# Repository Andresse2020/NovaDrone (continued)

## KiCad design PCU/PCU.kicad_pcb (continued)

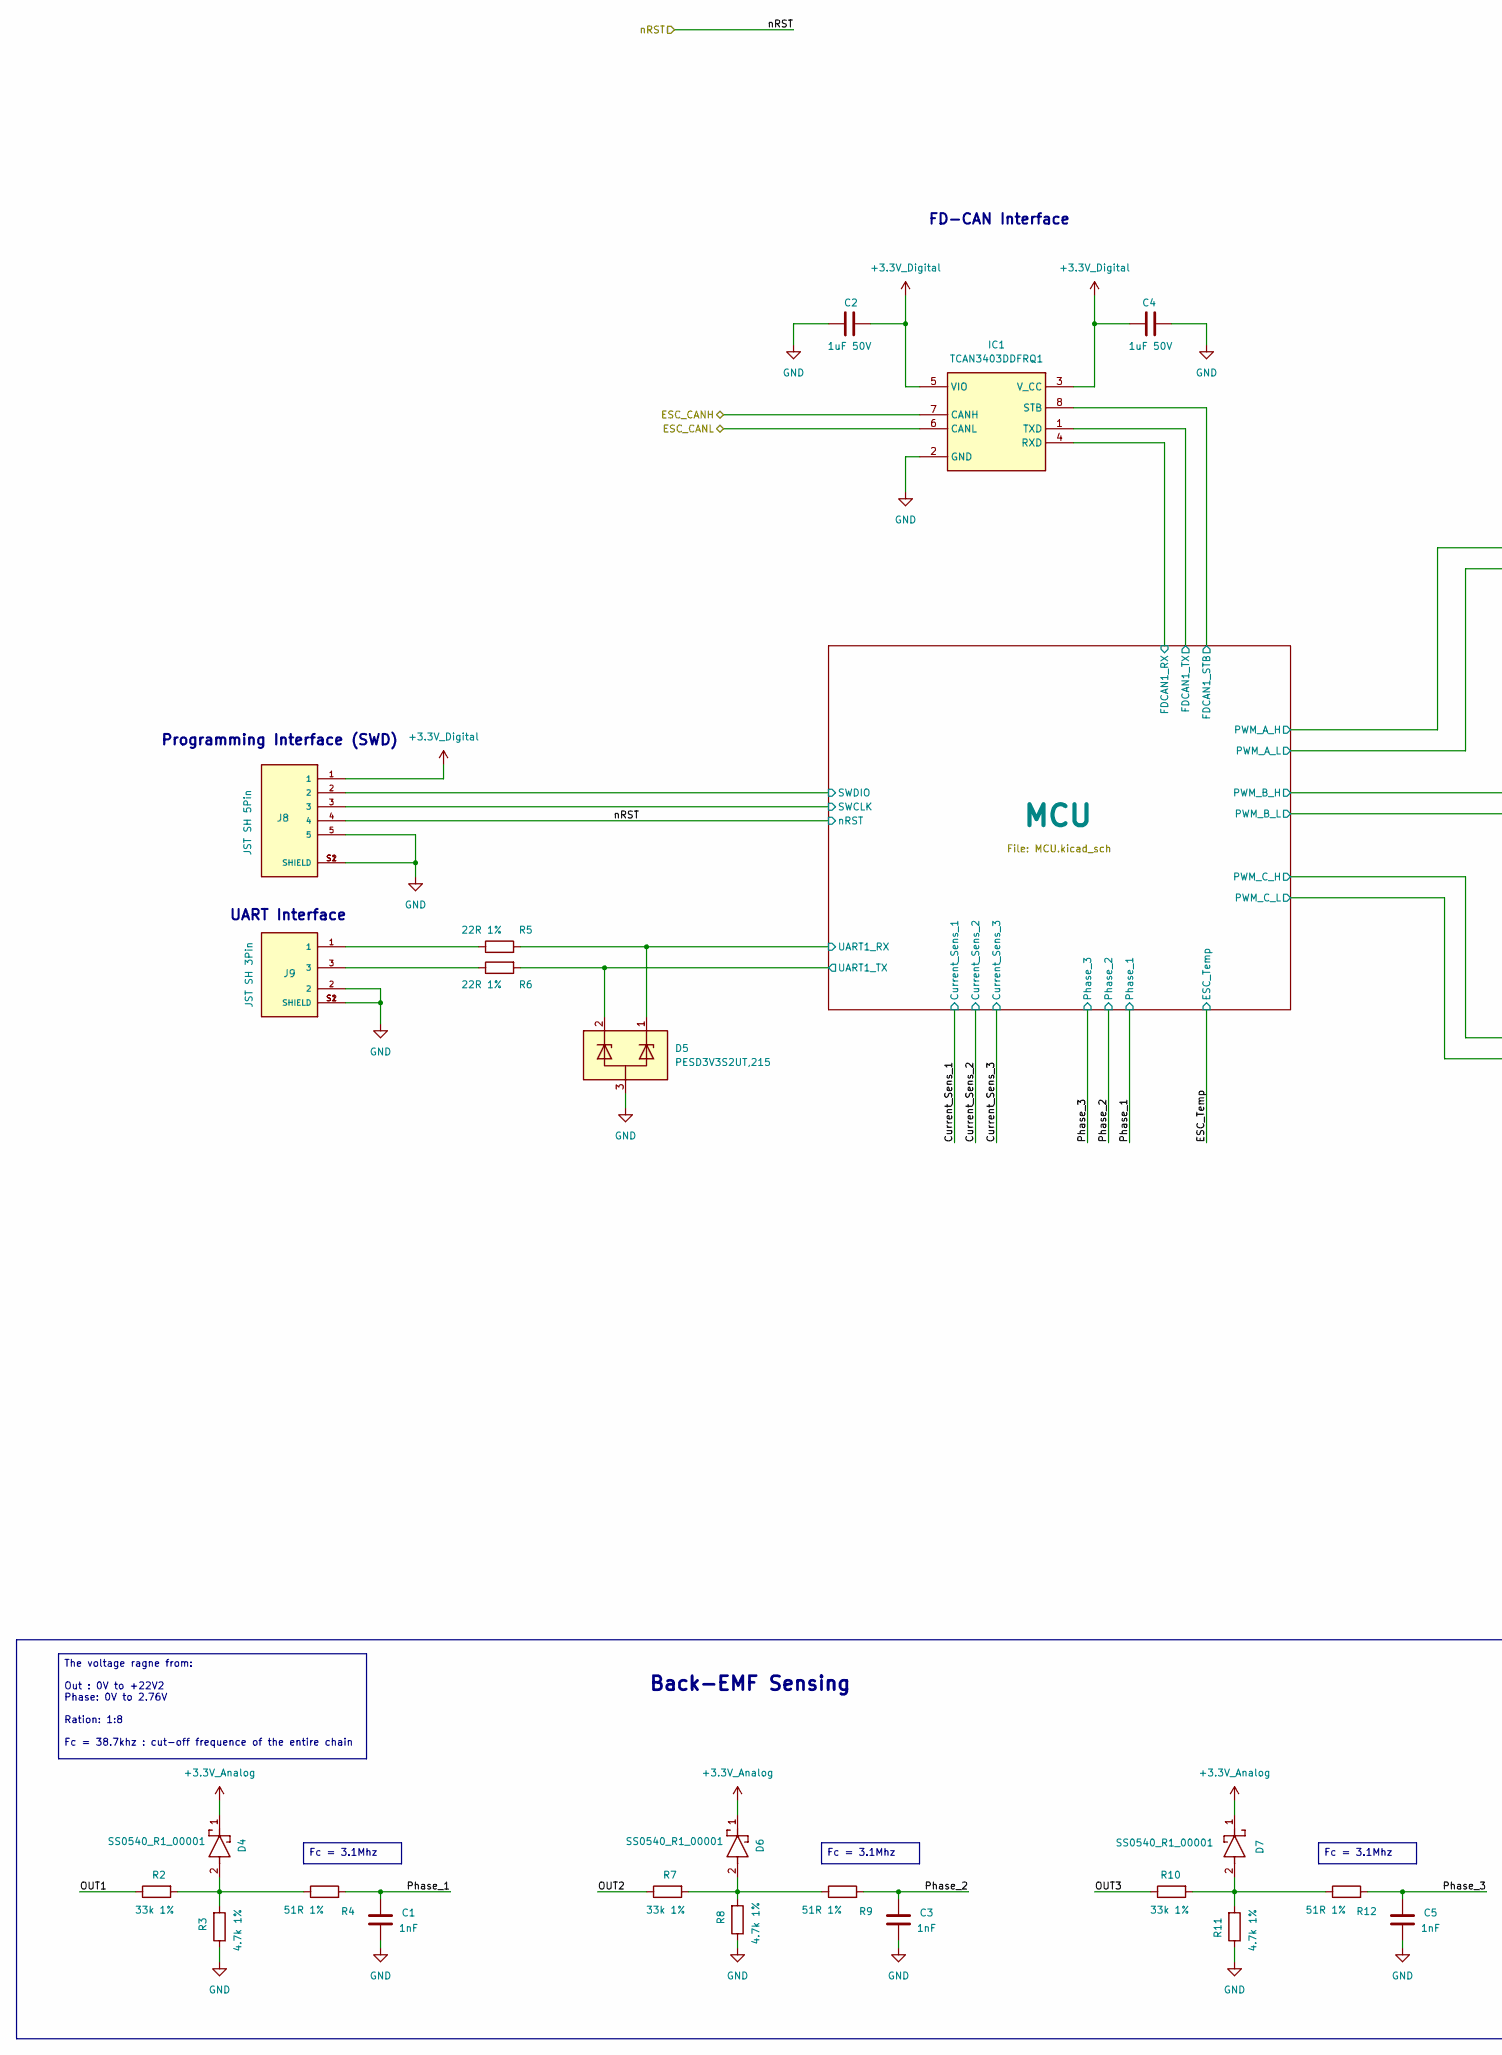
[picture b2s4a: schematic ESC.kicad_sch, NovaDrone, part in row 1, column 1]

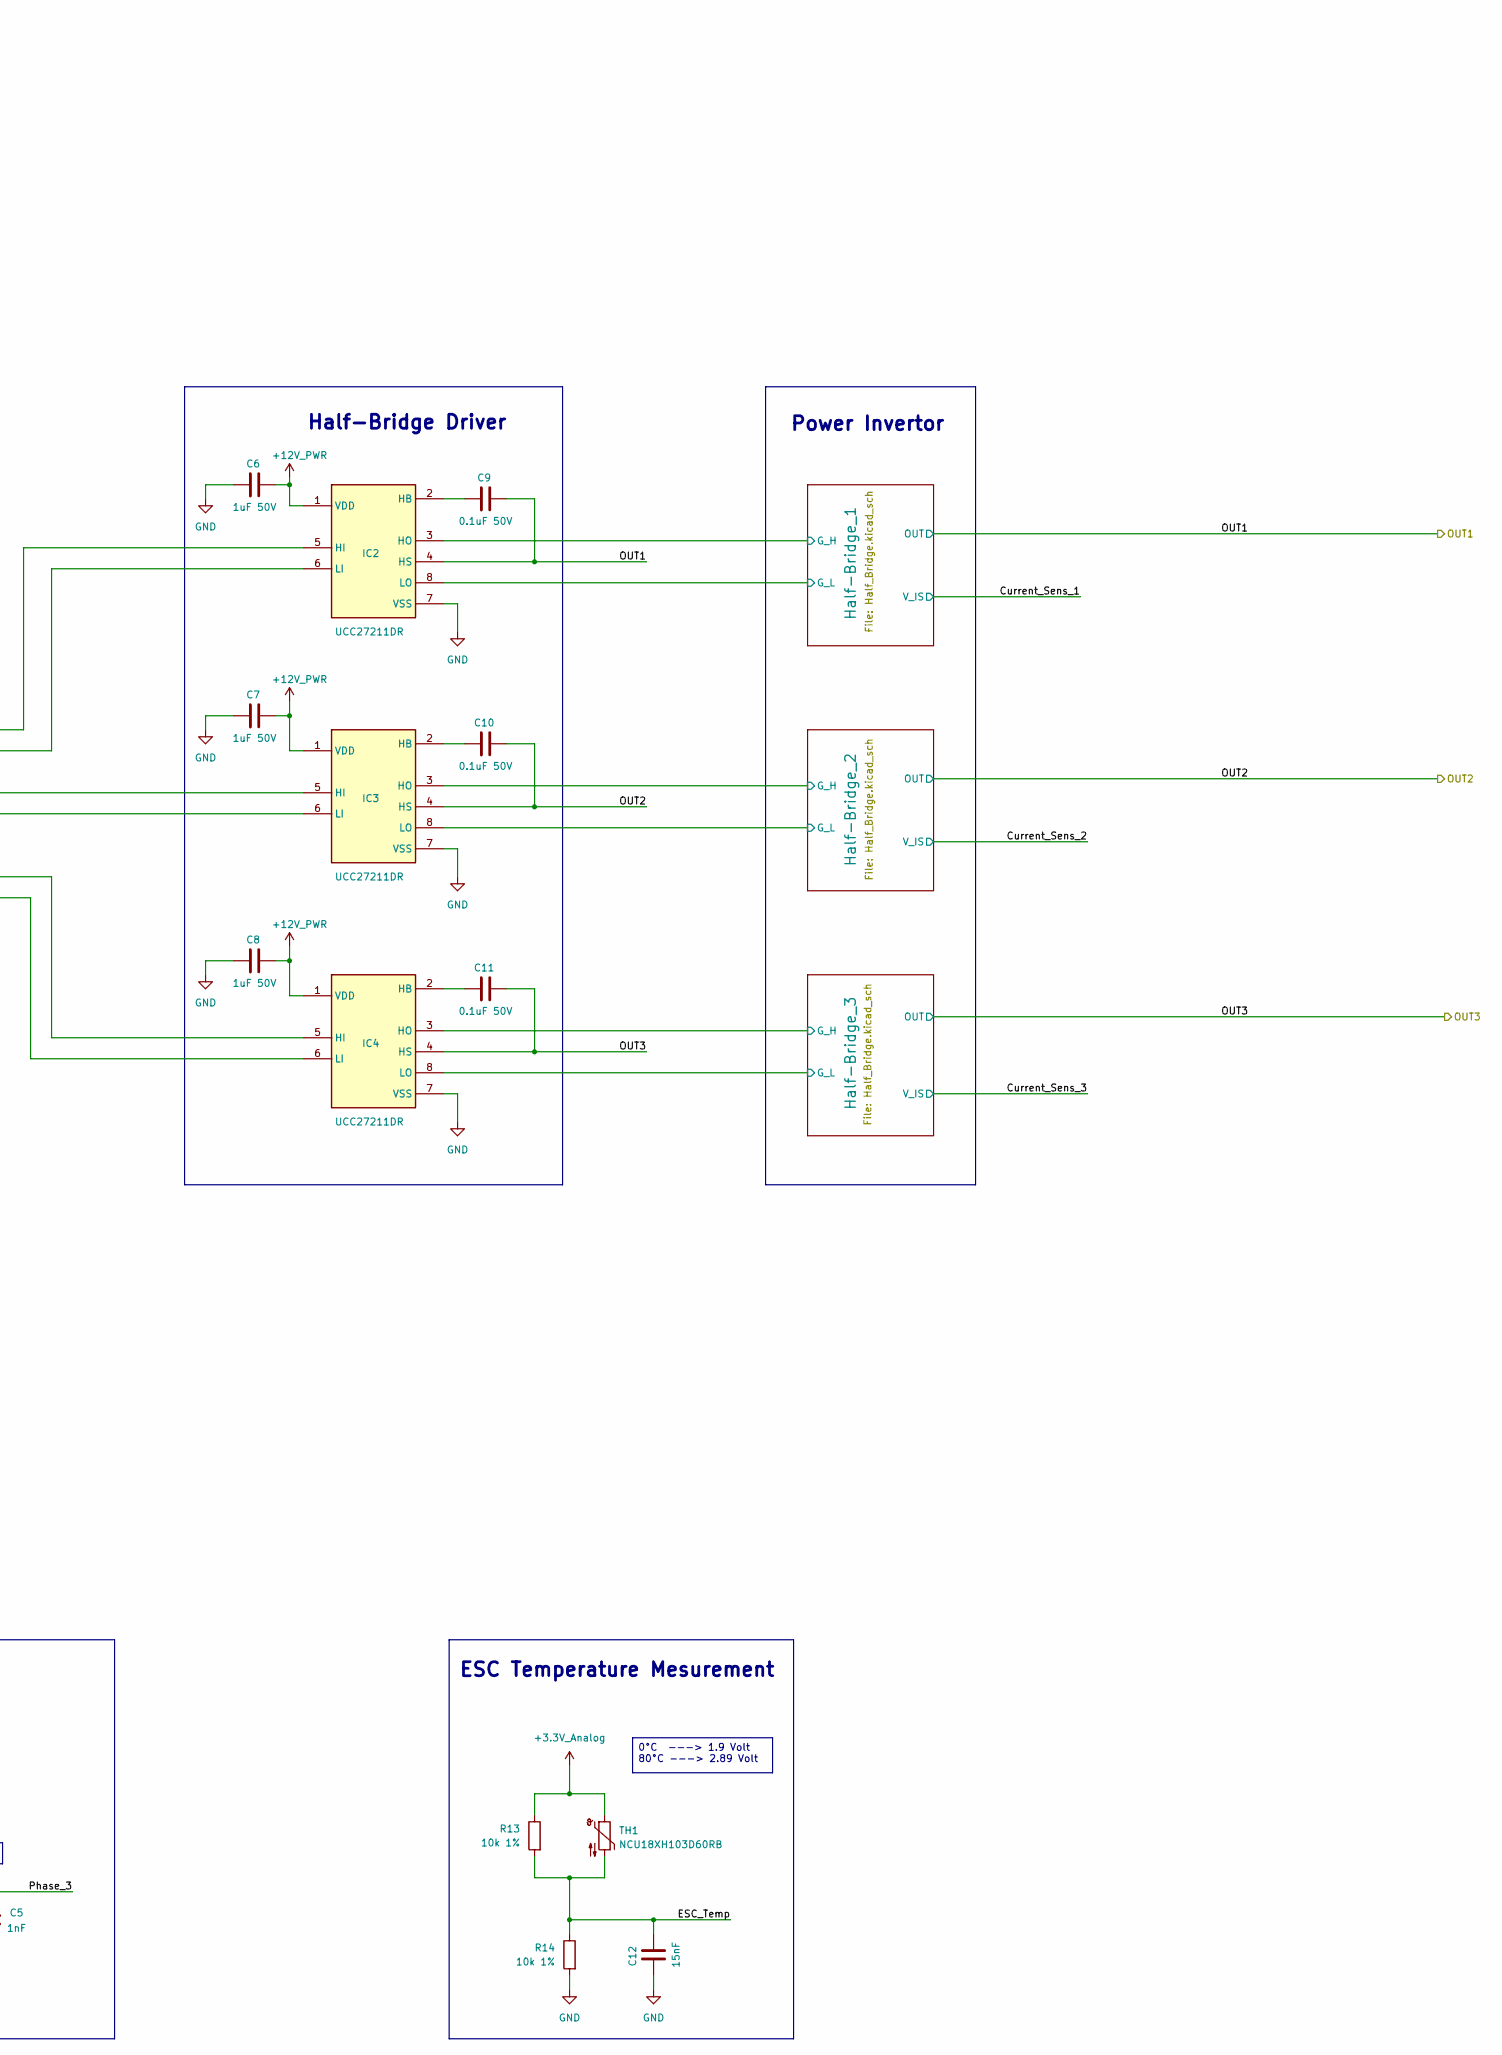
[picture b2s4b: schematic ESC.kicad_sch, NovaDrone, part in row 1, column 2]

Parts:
C1, C3, C5: 1nF; C_0603_1608Metric; Manufacturer_Part_Number KAF15AR71H102KM
C2, C4, C6, C7, C8: 1uF 50V; C_0805_2012Metric; Manufacturer_Part_Number CL21B105KBFNNNE
C9, C10, C11: 0.1uF 50V; C_0603_1608Metric; Manufacturer_Part_Number CL10B104KB85PNL
C12: 15nF; C_0603_1608Metric; Manufacturer_Part_Number CL10B153KB8NNNC
D4, D6, D7: SS0540_R1_00001; SOD3816X135N; Mouser Part Number 241-SS0540_R1_00001
D5: PESD3V3S2UT,215; SOT95P230X110-3N; Mouser Part Number 771-PESD3V3S2UT-T/R
IC1: TCAN3403DDFRQ1; SOT65P280X110-8N; Mouser Part Number 595-TCAN3403DDFRQ1
IC2, IC3, IC4: UCC27211DR; SOIC127P600X175-8N; Mouser Part Number 595-UCC27211DR
J8: JST SH 5Pin; JST_BM05B-SRSS-TB_LF__SN_; PARTREV N/A
J9: JST SH 3Pin; JST_BM03B-SRSS-TB_LF__SN_; PARTREV N/A
R2, R7, R10: 33k 1%; R_0603_1608Metric; Manufacturer_Part_Number AC0603FR-1333KL
R3, R8, R11: 4.7k 1%; R_0603_1608Metric; Manufacturer_Part_Number AF0603FR-074K7L
R4, R9, R12: 51R 1%; R_0603_1608Metric; Manufacturer_Part_Number RT0603FRE0751RL
R5, R6: 22R 1%; R_0603_1608Metric; Manufacturer_Part_Number RT0603FRD0722RL
R13, R14: 10k 1%; R_0603_1608Metric; Manufacturer_Part_Number AF0603FR-0710KL
TH1: NCU18XH103D60RB; R_0603_1608Metric; Manufacturer_Part_Number NCU18XH103D60RB

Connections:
+3.3V_Analog: D4.1 (K), D6.1 (K), D7.1 (K), R13.1, TH1.1; also elsewhere on the board
+3.3V_Digital: C2.1, C4.1, IC1.3 (V_CC), IC1.5 (VIO), J8.1; also elsewhere on the board
+12V_PWR: C6.2, C7.2, C8.2, IC2.1 (VDD), IC3.1 (VDD), IC4.1 (VDD); also elsewhere on the board
/CAN+: IC1.7 (CANH); also elsewhere on the board
/CAN-: IC1.6 (CANL); also elsewhere on the board
/ESC_1/ESC_Temp: C12.2, R13.2, R14.1, TH1.2; also elsewhere on the board
/ESC_1/Half-Bridge_1/G_H: IC2.3 (HO); also elsewhere on the board
/ESC_1/Half-Bridge_1/G_L: IC2.8 (LO); also elsewhere on the board
/ESC_1/Half-Bridge_2/G_H: IC3.3 (HO); also elsewhere on the board
/ESC_1/Half-Bridge_2/G_L: IC3.8 (LO); also elsewhere on the board
/ESC_1/Half-Bridge_3/G_H: IC4.3 (HO); also elsewhere on the board
/ESC_1/Half-Bridge_3/G_L: IC4.8 (LO); also elsewhere on the board
/ESC_1/MCU/FDCAN1_RX: IC1.4 (RXD); also elsewhere on the board
/ESC_1/MCU/FDCAN1_STB: IC1.8 (STB); also elsewhere on the board
/ESC_1/MCU/FDCAN1_TX: IC1.1 (TXD); also elsewhere on the board
/ESC_1/MCU/PWM_A_H: IC2.5 (HI); also elsewhere on the board
/ESC_1/MCU/PWM_A_L: IC2.6 (LI); also elsewhere on the board
/ESC_1/MCU/PWM_B_H: IC3.5 (HI); also elsewhere on the board
/ESC_1/MCU/PWM_B_L: IC3.6 (LI); also elsewhere on the board
/ESC_1/MCU/PWM_C_H: IC4.5 (HI); also elsewhere on the board
/ESC_1/MCU/PWM_C_L: IC4.6 (LI); also elsewhere on the board
/ESC_1/MCU/SWCLK: J8.3; also elsewhere on the board
/ESC_1/MCU/SWDIO: J8.2; also elsewhere on the board
/ESC_1/MCU/UART1_RX: D5.1, R5.2; also elsewhere on the board
/ESC_1/MCU/UART1_TX: D5.2, R6.2; also elsewhere on the board
/ESC_1/OUT1: C9.2, IC2.4 (HS), R2.1; also elsewhere on the board
/ESC_1/OUT2: C10.2, IC3.4 (HS), R7.1; also elsewhere on the board
/ESC_1/OUT3: C11.2, IC4.4 (HS), R10.1; also elsewhere on the board
/ESC_1/Phase_1: C1.2, R4.2; also elsewhere on the board
/ESC_1/Phase_2: C3.2, R9.2; also elsewhere on the board
/ESC_1/Phase_3: C5.2, R12.2; also elsewhere on the board
/ESC_1_nRST: J8.4; also elsewhere on the board
GND: C1.1, C2.2, C3.1, C4.2, C5.1, C6.1, C7.1, C8.1, C12.1, D5.3, IC1.2 (GND), IC2.7 (VSS), IC3.7 (VSS), IC4.7 (VSS), J8.5, J8.S1 (SHIELD), J8.S2 (SHIELD), J9.2, J9.S1 (SHIELD), J9.S2 (SHIELD), R3.1, R8.1, R11.1, R14.2; also elsewhere on the board
unnamed: D4.2 (A), R2.2, R3.2, R4.1
unnamed: D6.2 (A), R7.2, R8.2, R9.1
unnamed: D7.2 (A), R10.2, R11.2, R12.1
unnamed: C9.1, IC2.2 (HB)
unnamed: C10.1, IC3.2 (HB)
unnamed: C11.1, IC4.2 (HB)
unnamed: J9.1, R5.1
unnamed: J9.3, R6.1

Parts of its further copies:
C13, C15, C17, C61, C63, C65, C109, C111, C113: 1nF; C_0603_1608Metric; Manufacturer_Part_Number KAF15AR71H102KM
C14, C16, C18, C19, C20, C62, C64, C66, C67, C68, C110, C112, C114, C115, C116: 1uF 50V; C_0805_2012Metric; Manufacturer_Part_Number CL21B105KBFNNNE
C21, C22, C23, C69, C70, C71, C117, C118, C119: 0.1uF 50V; C_0603_1608Metric; Manufacturer_Part_Number CL10B104KB85PNL
C24, C72, C120: 15nF; C_0603_1608Metric; Manufacturer_Part_Number CL10B153KB8NNNC
D8, D10, D11, D18, D20, D21, D28, D30, D31: SS0540_R1_00001; SOD3816X135N; Mouser Part Number 241-SS0540_R1_00001
D9, D19, D29: PESD3V3S2UT,215; SOT95P230X110-3N; Mouser Part Number 771-PESD3V3S2UT-T/R
IC5, IC13, IC21: TCAN3403DDFRQ1; SOT65P280X110-8N; Mouser Part Number 595-TCAN3403DDFRQ1
IC6, IC7, IC8, IC14, IC15, IC16, IC22, IC23, IC24: UCC27211DR; SOIC127P600X175-8N; Mouser Part Number 595-UCC27211DR
J10, J12, J14: JST SH 5Pin; JST_BM05B-SRSS-TB_LF__SN_; PARTREV N/A
J11, J13, J15: JST SH 3Pin; JST_BM03B-SRSS-TB_LF__SN_; PARTREV N/A
R15, R20, R23, R73, R78, R81, R131, R136, R139: 33k 1%; R_0603_1608Metric; Manufacturer_Part_Number AC0603FR-1333KL
R16, R21, R24, R74, R79, R82, R132, R137, R140: 4.7k 1%; R_0603_1608Metric; Manufacturer_Part_Number AF0603FR-074K7L
R17, R22, R25, R75, R80, R83, R133, R138, R141: 51R 1%; R_0603_1608Metric; Manufacturer_Part_Number RT0603FRE0751RL
R18, R19, R76, R77, R134, R135: 22R 1%; R_0603_1608Metric; Manufacturer_Part_Number RT0603FRD0722RL
R26, R27, R84, R85, R142, R143: 10k 1%; R_0603_1608Metric; Manufacturer_Part_Number AF0603FR-0710KL
TH2, TH3, TH4: NCU18XH103D60RB; R_0603_1608Metric; Manufacturer_Part_Number NCU18XH103D60RB

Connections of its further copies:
+3.3V_Analog: D8.1 (K), D10.1 (K), D11.1 (K), D18.1 (K), D20.1 (K), D21.1 (K), D28.1 (K), D30.1 (K), D31.1 (K), R26.1, R84.1, R142.1, TH2.1, TH3.1, TH4.1; also elsewhere on the board
+3.3V_Digital: C14.1, C16.1, C62.1, C64.1, C110.1, C112.1, IC5.3 (V_CC), IC5.5 (VIO), IC13.3 (V_CC), IC13.5 (VIO), IC21.3 (V_CC), IC21.5 (VIO), J10.1, J12.1, J14.1; also elsewhere on the board
+12V_PWR: C18.2, C19.2, C20.2, C66.2, C67.2, C68.2, C114.2, C115.2, C116.2, IC6.1 (VDD), IC7.1 (VDD), IC8.1 (VDD), IC14.1 (VDD), IC15.1 (VDD), IC16.1 (VDD), IC22.1 (VDD), IC23.1 (VDD), IC24.1 (VDD); also elsewhere on the board
/CAN+: IC5.7 (CANH), IC13.7 (CANH), IC21.7 (CANH); also elsewhere on the board
/CAN-: IC5.6 (CANL), IC13.6 (CANL), IC21.6 (CANL); also elsewhere on the board
/ESC_2/ESC_Temp: C24.2, R26.2, R27.1, TH2.2; also elsewhere on the board
/ESC_2/Half-Bridge_1/G_H: IC6.3 (HO); also elsewhere on the board
/ESC_2/Half-Bridge_1/G_L: IC6.8 (LO); also elsewhere on the board
/ESC_2/Half-Bridge_2/G_H: IC7.3 (HO); also elsewhere on the board
/ESC_2/Half-Bridge_2/G_L: IC7.8 (LO); also elsewhere on the board
/ESC_2/Half-Bridge_3/G_H: IC8.3 (HO); also elsewhere on the board
/ESC_2/Half-Bridge_3/G_L: IC8.8 (LO); also elsewhere on the board
/ESC_2/MCU/FDCAN1_RX: IC5.4 (RXD); also elsewhere on the board
/ESC_2/MCU/FDCAN1_STB: IC5.8 (STB); also elsewhere on the board
/ESC_2/MCU/FDCAN1_TX: IC5.1 (TXD); also elsewhere on the board
/ESC_2/MCU/PWM_A_H: IC6.5 (HI); also elsewhere on the board
/ESC_2/MCU/PWM_A_L: IC6.6 (LI); also elsewhere on the board
/ESC_2/MCU/PWM_B_H: IC7.5 (HI); also elsewhere on the board
/ESC_2/MCU/PWM_B_L: IC7.6 (LI); also elsewhere on the board
/ESC_2/MCU/PWM_C_H: IC8.5 (HI); also elsewhere on the board
/ESC_2/MCU/PWM_C_L: IC8.6 (LI); also elsewhere on the board
/ESC_2/MCU/SWCLK: J10.3; also elsewhere on the board
/ESC_2/MCU/SWDIO: J10.2; also elsewhere on the board
/ESC_2/MCU/UART1_RX: D9.1, R18.2; also elsewhere on the board
/ESC_2/MCU/UART1_TX: D9.2, R19.2; also elsewhere on the board
/ESC_2/OUT1: C21.2, IC6.4 (HS), R15.1; also elsewhere on the board
/ESC_2/OUT2: C22.2, IC7.4 (HS), R20.1; also elsewhere on the board
/ESC_2/OUT3: C23.2, IC8.4 (HS), R23.1; also elsewhere on the board
/ESC_2/Phase_1: C13.2, R17.2; also elsewhere on the board
/ESC_2/Phase_2: C15.2, R22.2; also elsewhere on the board
/ESC_2/Phase_3: C17.2, R25.2; also elsewhere on the board
/ESC_2_nRST: J10.4; also elsewhere on the board
/ESC_3/ESC_Temp: C72.2, R84.2, R85.1, TH3.2; also elsewhere on the board
/ESC_3/Half-Bridge_1/G_H: IC14.3 (HO); also elsewhere on the board
/ESC_3/Half-Bridge_1/G_L: IC14.8 (LO); also elsewhere on the board
/ESC_3/Half-Bridge_2/G_H: IC15.3 (HO); also elsewhere on the board
/ESC_3/Half-Bridge_2/G_L: IC15.8 (LO); also elsewhere on the board
/ESC_3/Half-Bridge_3/G_H: IC16.3 (HO); also elsewhere on the board
/ESC_3/Half-Bridge_3/G_L: IC16.8 (LO); also elsewhere on the board
/ESC_3/MCU/FDCAN1_RX: IC13.4 (RXD); also elsewhere on the board
/ESC_3/MCU/FDCAN1_STB: IC13.8 (STB); also elsewhere on the board
/ESC_3/MCU/FDCAN1_TX: IC13.1 (TXD); also elsewhere on the board
/ESC_3/MCU/PWM_A_H: IC14.5 (HI); also elsewhere on the board
/ESC_3/MCU/PWM_A_L: IC14.6 (LI); also elsewhere on the board
/ESC_3/MCU/PWM_B_H: IC15.5 (HI); also elsewhere on the board
/ESC_3/MCU/PWM_B_L: IC15.6 (LI); also elsewhere on the board
/ESC_3/MCU/PWM_C_H: IC16.5 (HI); also elsewhere on the board
/ESC_3/MCU/PWM_C_L: IC16.6 (LI); also elsewhere on the board
/ESC_3/MCU/SWCLK: J12.3; also elsewhere on the board
/ESC_3/MCU/SWDIO: J12.2; also elsewhere on the board
/ESC_3/MCU/UART1_RX: D19.1, R76.2; also elsewhere on the board
/ESC_3/MCU/UART1_TX: D19.2, R77.2; also elsewhere on the board
/ESC_3/OUT1: C69.2, IC14.4 (HS), R73.1; also elsewhere on the board
/ESC_3/OUT2: C70.2, IC15.4 (HS), R78.1; also elsewhere on the board
/ESC_3/OUT3: C71.2, IC16.4 (HS), R81.1; also elsewhere on the board
/ESC_3/Phase_1: C61.2, R75.2; also elsewhere on the board
/ESC_3/Phase_2: C63.2, R80.2; also elsewhere on the board
/ESC_3/Phase_3: C65.2, R83.2; also elsewhere on the board
/ESC_3_nRST: J12.4; also elsewhere on the board
/ESC_4/ESC_Temp: C120.2, R142.2, R143.1, TH4.2; also elsewhere on the board
/ESC_4/Half-Bridge_1/G_H: IC22.3 (HO); also elsewhere on the board
/ESC_4/Half-Bridge_1/G_L: IC22.8 (LO); also elsewhere on the board
/ESC_4/Half-Bridge_2/G_H: IC23.3 (HO); also elsewhere on the board
/ESC_4/Half-Bridge_2/G_L: IC23.8 (LO); also elsewhere on the board
/ESC_4/Half-Bridge_3/G_H: IC24.3 (HO); also elsewhere on the board
/ESC_4/Half-Bridge_3/G_L: IC24.8 (LO); also elsewhere on the board
/ESC_4/MCU/FDCAN1_RX: IC21.4 (RXD); also elsewhere on the board
/ESC_4/MCU/FDCAN1_STB: IC21.8 (STB); also elsewhere on the board
/ESC_4/MCU/FDCAN1_TX: IC21.1 (TXD); also elsewhere on the board
/ESC_4/MCU/PWM_A_H: IC22.5 (HI); also elsewhere on the board
/ESC_4/MCU/PWM_A_L: IC22.6 (LI); also elsewhere on the board
/ESC_4/MCU/PWM_B_H: IC23.5 (HI); also elsewhere on the board
/ESC_4/MCU/PWM_B_L: IC23.6 (LI); also elsewhere on the board
/ESC_4/MCU/PWM_C_H: IC24.5 (HI); also elsewhere on the board
/ESC_4/MCU/PWM_C_L: IC24.6 (LI); also elsewhere on the board
/ESC_4/MCU/SWCLK: J14.3; also elsewhere on the board
/ESC_4/MCU/SWDIO: J14.2; also elsewhere on the board
/ESC_4/MCU/UART1_RX: D29.1, R134.2; also elsewhere on the board
/ESC_4/MCU/UART1_TX: D29.2, R135.2; also elsewhere on the board
/ESC_4/OUT1: C117.2, IC22.4 (HS), R131.1; also elsewhere on the board
/ESC_4/OUT2: C118.2, IC23.4 (HS), R136.1; also elsewhere on the board
/ESC_4/OUT3: C119.2, IC24.4 (HS), R139.1; also elsewhere on the board
/ESC_4/Phase_1: C109.2, R133.2; also elsewhere on the board
/ESC_4/Phase_2: C111.2, R138.2; also elsewhere on the board
/ESC_4/Phase_3: C113.2, R141.2; also elsewhere on the board
/ESC_4_nRST: J14.4; also elsewhere on the board
GND: C13.1, C14.2, C15.1, C16.2, C17.1, C18.1, C19.1, C20.1, C24.1, C61.1, C62.2, C63.1, C64.2, C65.1, C66.1, C67.1, C68.1, C72.1, C109.1, C110.2, C111.1, C112.2, C113.1, C114.1, C115.1, C116.1, C120.1, D9.3, D19.3, D29.3, IC5.2 (GND), IC6.7 (VSS), IC7.7 (VSS), IC8.7 (VSS), IC13.2 (GND), IC14.7 (VSS), IC15.7 (VSS), IC16.7 (VSS), IC21.2 (GND), IC22.7 (VSS), IC23.7 (VSS), IC24.7 (VSS), J10.5, J10.S1 (SHIELD), J10.S2 (SHIELD), J11.2, J11.S1 (SHIELD), J11.S2 (SHIELD), J12.5, J12.S1 (SHIELD), J12.S2 (SHIELD), J13.2, J13.S1 (SHIELD), J13.S2 (SHIELD), J14.5, J14.S1 (SHIELD), J14.S2 (SHIELD), J15.2, J15.S1 (SHIELD), J15.S2 (SHIELD), R16.1, R21.1, R24.1, R27.2, R74.1, R79.1, R82.1, R85.2, R132.1, R137.1, R140.1, R143.2; also elsewhere on the board
unnamed: D8.2 (A), R15.2, R16.2, R17.1
unnamed: D10.2 (A), R20.2, R21.2, R22.1
unnamed: D11.2 (A), R23.2, R24.2, R25.1
unnamed: D18.2 (A), R73.2, R74.2, R75.1
unnamed: D20.2 (A), R78.2, R79.2, R80.1
unnamed: D21.2 (A), R81.2, R82.2, R83.1
unnamed: D28.2 (A), R131.2, R132.2, R133.1
unnamed: D30.2 (A), R136.2, R137.2, R138.1
unnamed: D31.2 (A), R139.2, R140.2, R141.1
unnamed: C21.1, IC6.2 (HB)
unnamed: C22.1, IC7.2 (HB)
unnamed: C23.1, IC8.2 (HB)
unnamed: C69.1, IC14.2 (HB)
unnamed: C70.1, IC15.2 (HB)
unnamed: C71.1, IC16.2 (HB)
unnamed: C117.1, IC22.2 (HB)
unnamed: C118.1, IC23.2 (HB)
unnamed: C119.1, IC24.2 (HB)
unnamed: J11.1, R18.1
unnamed: J11.3, R19.1
unnamed: J13.1, R76.1
unnamed: J13.3, R77.1
unnamed: J15.1, R134.1
unnamed: J15.3, R135.1

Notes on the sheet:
UART Interface
FD-CAN Interface
Back-EMF Sensing
ESC Temperature Mesurement
Power Invertor
Programming Interface (SWD)
Half-Bridge Driver
Fc = 3.1Mhz
0°C ---> 1.9 Volt 80°C ---> 2.89 Volt
The voltage ragne from: Out : 0V to +22V2 Phase: 0V to 2.76V Ration: 1:8 Fc = 38.7khz : cut-off frequence of the entire chain

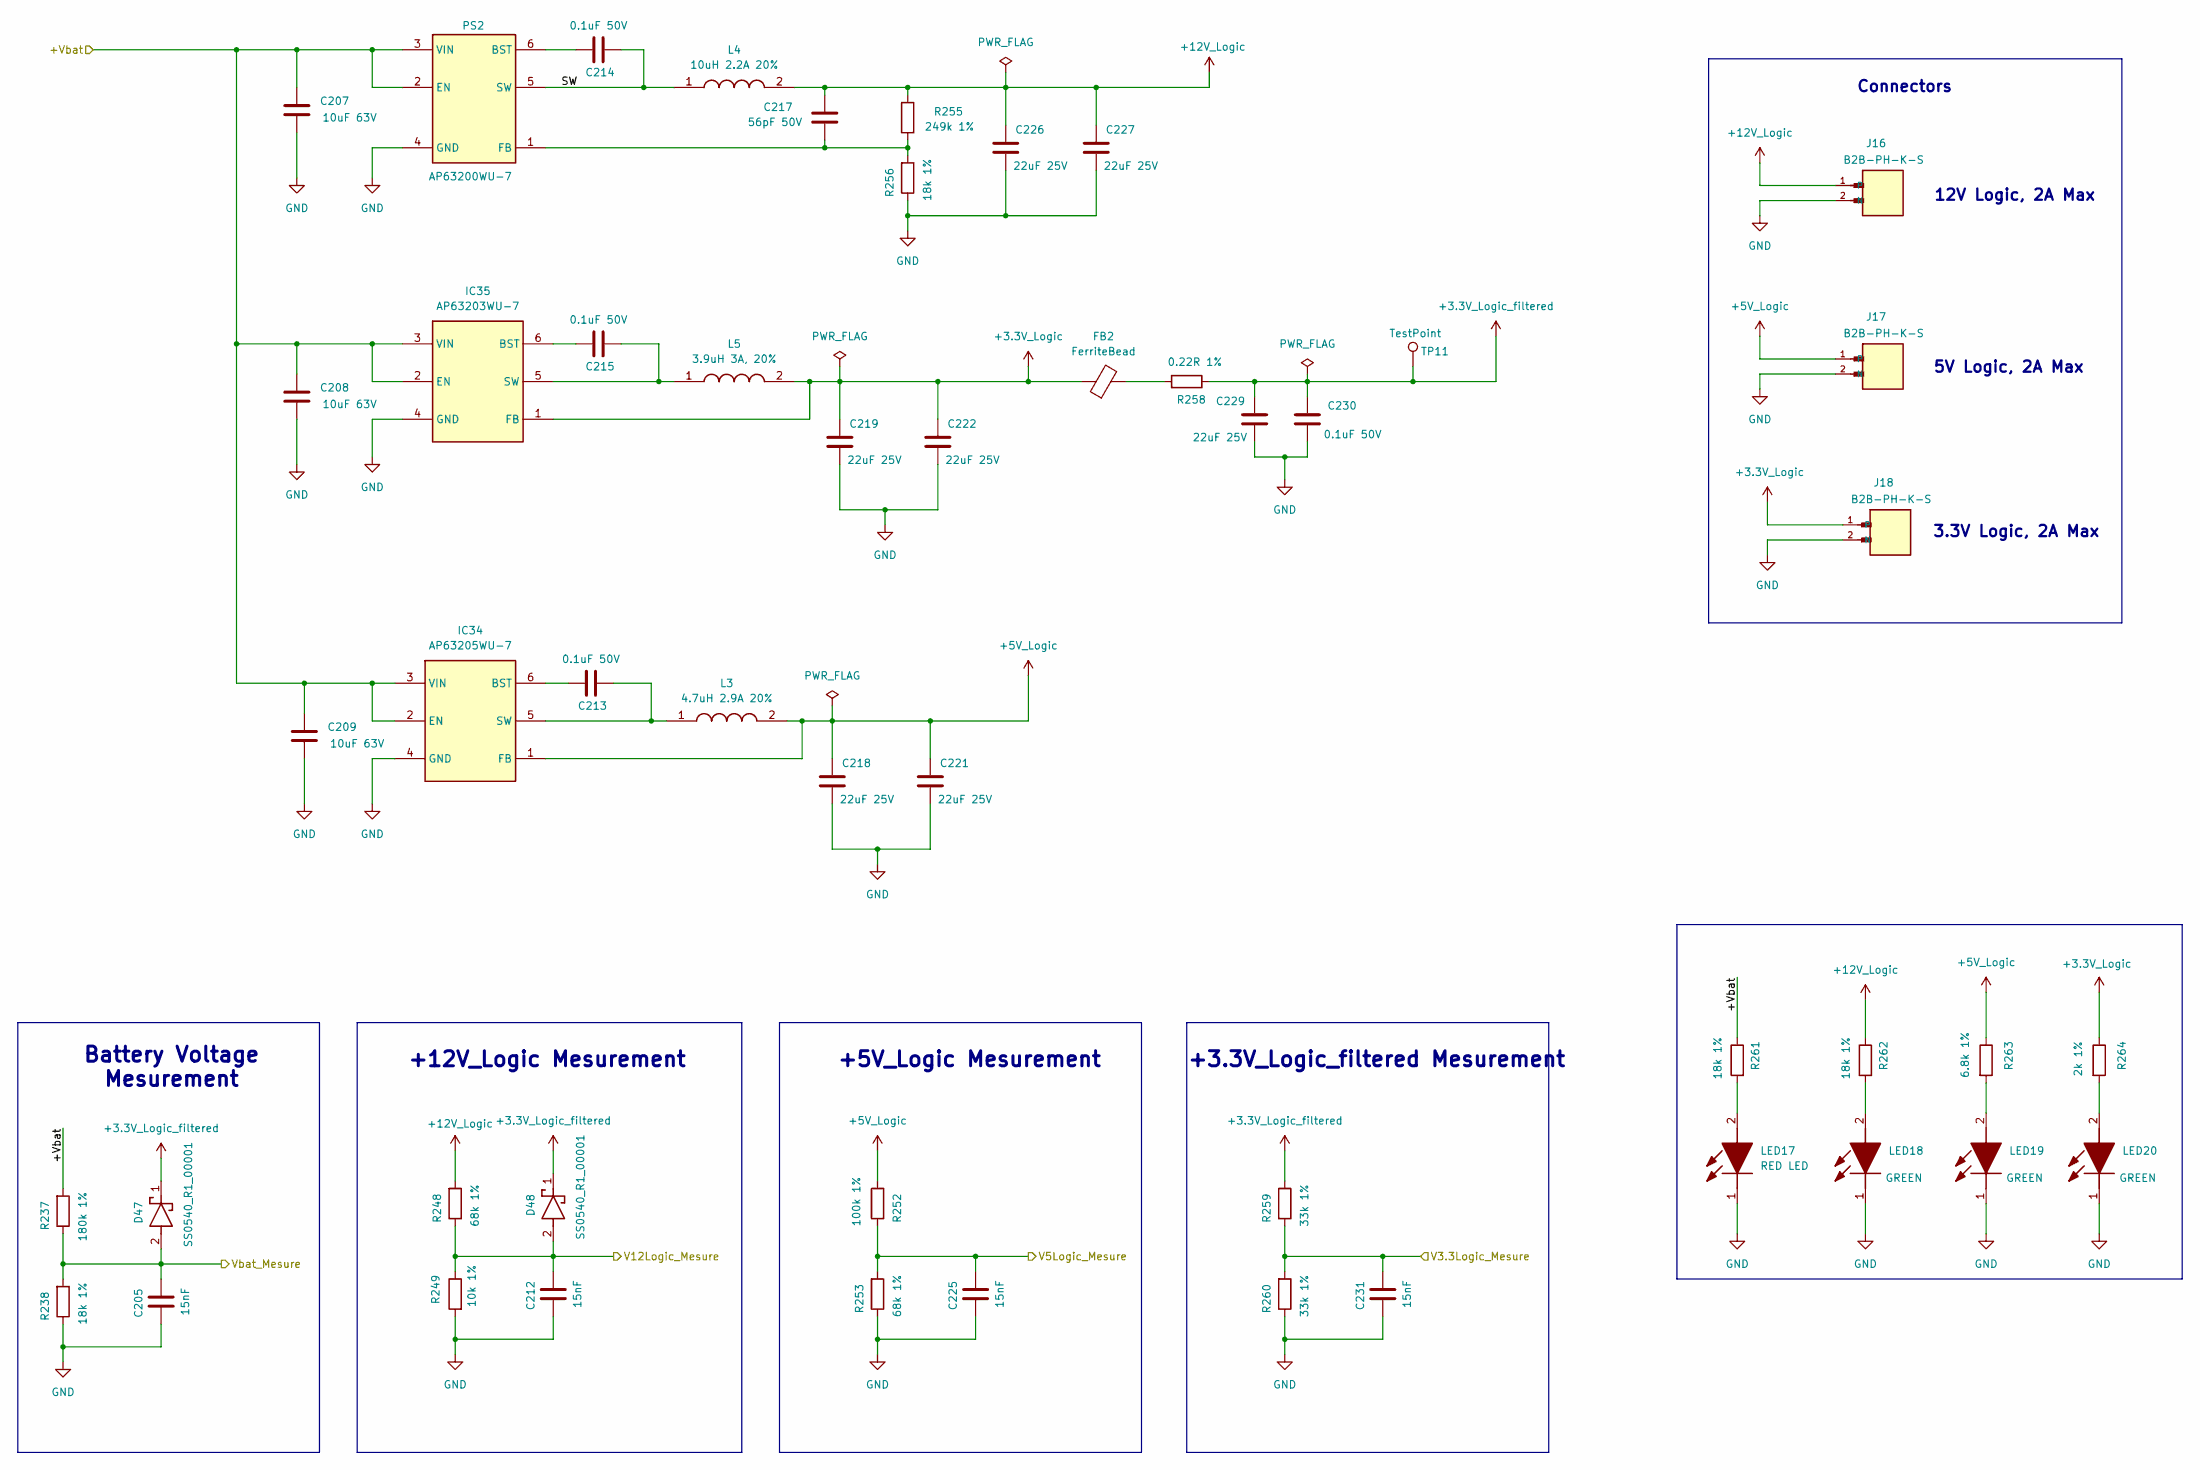
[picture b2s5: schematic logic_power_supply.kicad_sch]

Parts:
C205, C212, C225, C231: 15nF; C_0603_1608Metric; Manufacturer_Part_Number CL10B153KB8NNNC
C207, C208, C209: 10uF 63V; C_1210_3225Metric; Manufacturer_Part_Number CL32B106KMVNNWE
C213, C214, C215, C230: 0.1uF 50V; C_0603_1608Metric; Manufacturer_Part_Number CL10B104KB85PNL
C217: 56pF 50V; C_0603_1608Metric; Manufacturer_Part_Number CL10C560JB8NNNC
C218, C219, C221, C222, C226, C227, C229: 22uF 25V; C_1210_3225Metric; Manufacturer_Part_Number CL32B226KAJNNNE
D47, D48: SS0540_R1_00001; SOD3816X135N; Mouser Part Number 241-SS0540_R1_00001
FB2: FerriteBead; L_0805_2012Metric; Manufacturer_Part_Number MPZ2012S601AT000
IC34: AP63205WU-7; AP63205WU7; Mouser Part Number 621-AP63205WU-7
IC35: AP63203WU-7; AP63203WU7; Mouser Part Number 621-AP63203WU-7
J16, J17, J18: B2B-PH-K-S; JST_B2B-PH-K-S
L3: 4.7uH 2.9A 20%; ASPI-4030S; Mouser Part Number 815-ASPI-4030S-4R7MT
L4: 10uH 2.2A 20%; BWVS00505040100M00; Manufacturer_Part_Number BWVS00505040100M00
L5: 3.9uH 3A, 20%; ASPI0628150MT1; Mouser Part Number 815-ASPI-0628-3R9MT1
LED17: RED LED; LEDM168X80N; Manufacturer_Part_Number APHD1608LSURCK
LED18, LED19, LED20: GREEN; LEDM168X80N; Mouser Part Number 604-APHD1608LZGCK
PS2: AP63200WU-7; SOT95P280X100-6N; Mouser Part Number 621-AP63200WU-7
R237: 180k 1%; R_0603_1608Metric; Manufacturer_Part_Number RT0603FRE07180KL
R238, R256, R261, R262: 18k 1%; R_0603_1608Metric; Manufacturer_Part_Number AC0603FR-1318KL
R248, R253: 68k 1%; R_0603_1608Metric; Manufacturer_Part_Number RC0603FR-1068KL
R249: 10k 1%; R_0603_1608Metric; Manufacturer_Part_Number AF0603FR-0710KL
R252: 100k 1%; R_0603_1608Metric; Manufacturer_Part_Number AT0603FRE07100KL
R255: 249k 1%; R_0603_1608Metric; Manufacturer_Part_Number AF0603FR-07249KL
R258: 0.22R 1%; R_0805_2012Metric; Manufacturer_Part_Number RL0805FR-7W0R22L
R259, R260: 33k 1%; R_0603_1608Metric; Manufacturer_Part_Number AC0603FR-1333KL
R263: 6.8k 1%; R_0603_1608Metric; Manufacturer_Part_Number AC0603FR-076K8L
R264: 2k 1%; R_0603_1608Metric; Manufacturer_Part_Number RE0603FRE072KL
TP11: TestPoint; TestPoint_Pad_D1.0mm

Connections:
+3.3V_Logic: C219.2, C222.2, FB2.1, IC35.1 (FB), J18.1, L5.2, R264.1
+3.3V_Logic_filtered: C229.2, C230.2, D47.1 (K), D48.1 (K), R258.1, R259.2, TP11.1; also elsewhere on the board
+5V_Logic: C218.2, C221.2, IC34.1 (FB), J17.1, L3.2, R252.2, R263.1
+12V_Logic: C217.2, C226.2, C227.2, J16.1, L4.2, R248.2, R255.2, R262.1
/+Vbat: C207.2, C208.2, C209.2, IC34.2 (EN), IC34.3 (VIN), IC35.2 (EN), IC35.3 (VIN), PS2.2 (EN), PS2.3 (VIN), R237.2, R261.1; also elsewhere on the board
/Logic PSU/SW: C214.1, L4.1, PS2.5 (SW)
/Logic PSU/V3.3Logic_Mesure: C231.2, R259.1, R260.2; also elsewhere on the board
/Logic PSU/V5Logic_Mesure: C225.2, R252.1, R253.2; also elsewhere on the board
/Logic PSU/V12Logic_Mesure: C212.2, D48.2 (A), R248.1, R249.1; also elsewhere on the board
/Logic PSU/Vbat_Mesure: C205.2, D47.2 (A), R237.1, R238.2; also elsewhere on the board
GND: C205.1, C207.1, C208.1, C209.1, C212.1, C218.1, C219.1, C221.1, C222.1, C225.1, C226.1, C227.1, C229.1, C230.1, C231.1, IC34.4 (GND), IC35.4 (GND), J16.2 (N), J17.2 (N), J18.2 (N), LED17.1 (K), LED18.1 (K), LED19.1 (K), LED20.1 (K), PS2.4 (GND), R238.1, R249.2, R253.1, R256.1, R260.1; also elsewhere on the board
unnamed: FB2.2, R258.2
unnamed: C213.2, IC34.6 (BST)
unnamed: C213.1, IC34.5 (SW), L3.1
unnamed: C215.2, IC35.6 (BST)
unnamed: C215.1, IC35.5 (SW), L5.1
unnamed: LED17.2 (A), R261.2
unnamed: LED18.2 (A), R262.2
unnamed: LED19.2 (A), R263.2
unnamed: LED20.2 (A), R264.2
unnamed: C214.2, PS2.6 (BST)
unnamed: C217.1, PS2.1 (FB), R255.1, R256.2

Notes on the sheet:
Battery Voltage Mesurement
+3.3V_Logic_filtered Mesurement
5V Logic, 2A Max
Connectors
+12V_Logic Mesurement
+5V_Logic Mesurement
3.3V Logic, 2A Max
12V Logic, 2A Max
